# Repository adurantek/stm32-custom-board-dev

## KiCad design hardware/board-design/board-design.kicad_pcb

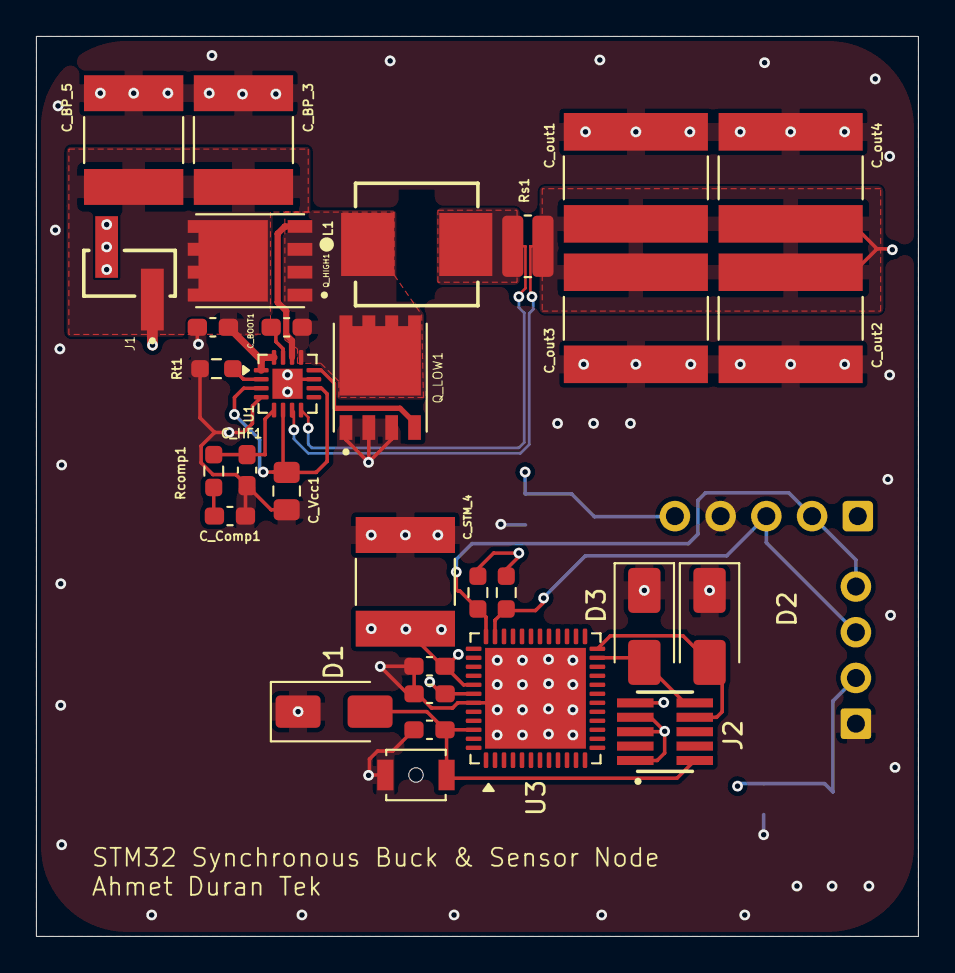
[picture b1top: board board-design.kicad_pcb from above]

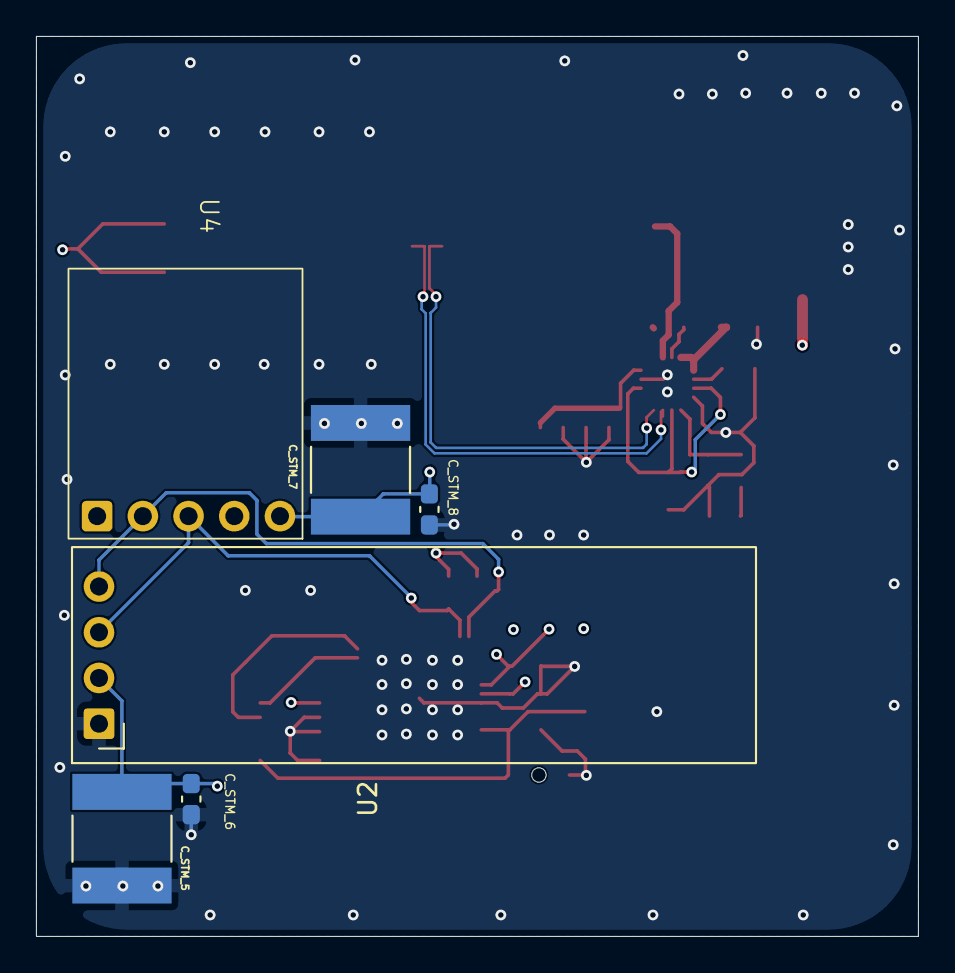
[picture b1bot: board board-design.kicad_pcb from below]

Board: 4 copper layers, 49.0 x 50.0 mm, 37 parts (6 on the bottom side), 17 nets.

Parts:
C_BOOT1: 0.1uF; C_0603_1608Metric_Pad1.08x0.95mm_HandSolder
C_BP_3, C_BP_5: 10uF; CAPC6153X390N
C_BP_4: 0.1uF; C_0603_1608Metric_Pad1.08x0.95mm_HandSolder
C_Comp1: 15nF; C_0603_1608Metric_Pad1.08x0.95mm_HandSolder
C_HF1: 100pF; C_0603_1608Metric_Pad1.08x0.95mm_HandSolder
C_STM_1, C_STM_2, C_STM_3, C_STM_6, C_STM_8: 0.1uF; C_0603_1608Metric_Pad1.08x0.95mm_HandSolder
C_STM_4, C_STM_5, C_STM_7: 10uF; CAPC6153X390N
C_Vcc1: 4.7uF; C_0805_2012Metric_Pad1.18x1.45mm_HandSolder
C_out1, C_out2, C_out3, C_out4: 47uF; CAPC6075X690N
D1, D2, D3: D_TVS; D_SMA
J1: Conn_01x02_Pin; SAMTEC_TSM-102-01-X-SV
J2: Conn_02x05_Odd_Even; SAMTEC_FTE-105-01-G-DV
L1: 1.5uH; WE-LHMI_7030
Q_HIGH1: CSD19532Q5B; TRANS_CSD19532Q5B
Q_LOW1: CSD19532Q5B; TRANS_CSD19532Q5B
R_OpenDrain1, R_OpenDrain2: 4.7k; R_0603_1608Metric_Pad0.98x0.95mm_HandSolder
Rcomp1: 6.04k; R_0603_1608Metric_Pad0.98x0.95mm_HandSolder
Rs1: 3m; R_0612_1632Metric_Pad1.18x3.40mm_HandSolder
Rt1: 53.6k; R_0603_1608Metric_Pad0.98x0.95mm_HandSolder
SW1: SW_Push; SW_SPST_B3U-1000P-B
U1: LM25139; VQFN-16-1EP_3x3mm_P0.5mm_EP1.68x1.68mm
U2: ER_OLEDM0.91_1x-I2C
U3: STM32C031C6Ux; QFN-48-1EP_7x7mm_P0.5mm_EP5.6x5.6mm
U4: BMP180; GY-68

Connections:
/DC-DC-Buck-Converter/V_INPUT: C_BP_3.1, C_BP_4.1, C_BP_5.1, J1.01 (Pin_1), Q_HIGH1.5_8, U1.1 (Vin), U1.16 (EN)
/DC-DC-Buck-Converter/V_OUT: C_STM_1.2, C_STM_3.2, C_STM_4.2, C_STM_5.1, C_STM_6.1, C_STM_7.1, C_STM_8.2, C_out1.1, C_out2.1, C_out3.1, C_out4.1, J2.01 (Pin_1), R_OpenDrain1.2, R_OpenDrain2.2, Rs1.2, U1.7 (Vout), U2.2 (VCC), U3.5 (VREF+), U3.6 (VDD), U4.1 (Vcc)
/DC-DC-Buck-Converter/Vcc: C_Vcc1.1, U1.3 (FPWM/SYNC), U1.6 (FB), U1.10 (Vcc)
/STM32/NRST: C_STM_2.1, D1.2 (A2), J2.10, SW1.2, U3.10 (PF2)
GND: C_BP_3.2, C_BP_4.2, C_BP_5.2, C_Comp1.1, C_HF1.2, C_STM_1.1, C_STM_2.2, C_STM_3.1, C_STM_4.1, C_STM_5.2, C_STM_6.2, C_STM_7.2, C_STM_8.1, C_Vcc1.2, C_out1.2, C_out2.2, C_out3.2, C_out4.2, D1.1 (A1), D2.1 (A1), D3.1 (A1), J1.02 (Pin_2), J2.03 (Pin_3), J2.05 (Pin_5), J2.09 (Pin_9), Q_LOW1.1, Q_LOW1.2, Q_LOW1.3, Rt1.1, SW1.1, U1.4 (AGND), U1.11 (PGND), U1.17 (Exposed_Pad), U2.1 (GND), U3.7 (VSS), U3.49 (VSS), U4.2 (GND)
unnamed: C_Comp1.2, Rcomp1.1
unnamed: D2.2 (A2), J2.04 (Pin_4), U3.36 (PA14)
unnamed: D3.2 (A2), J2.02 (Pin_2), U3.35 (PA13)
unnamed: C_BOOT1.2, U1.15 (CBOOT)
unnamed: C_HF1.1, Rcomp1.2, U1.5 (COMP)
unnamed: Q_HIGH1.4, U1.14 (HO)
unnamed: L1.2, Rs1.1, U1.8 (ISNS)
unnamed: Q_LOW1.4, U1.12 (LO)
unnamed: Rt1.2, U1.2 (RT)
unnamed: C_BOOT1.1, L1.1, Q_HIGH1.1, Q_HIGH1.2, Q_HIGH1.3, Q_LOW1.5_8, U1.13 (SW)
unnamed: R_OpenDrain2.1, U2.3 (SCL), U3.47 (PB8), U4.3 (SCL)
unnamed: R_OpenDrain1.1, U2.4 (SDA), U3.48 (PB9), U4.4 (SDA)
